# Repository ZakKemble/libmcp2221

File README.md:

# MCP2221 HID Library

This is a library for interfacing with the HID features of the [MCP2221 USB to UART and I2C/SMBus serial converter from Microchip](http://www.microchip.com/wwwproducts/Devices.aspx?product=MCP2221). The converter includes 4 GPIO pins, 3x 10-bit ADCs, 1x 5-bit DAC and more.

Microchip does provide a library for interfacing with the chip, however it is supplied as proprietary DLLs. This project aims to be an open-source and multi-platform alternative.

This library also makes use of [HIDAPI](http://www.signal11.us/oss/hidapi/).

| Feature | Status
| ------- | ------
| ADC     | Supported
| DAC     | Supported
| GPIO    | Supported
| Interrupt input        | Supported
| Clock reference output | Supported
| USB Descriptors (Manufacturer, product, serial, VID, PID) | Supported
| I2C/SMB | Limited support, WIP
| Flash password protection | Not yet implemented
| C++ and C# wrappers       | Not yet implemented

*Reading clock out duty cycle is not documented in the datasheet, but the Microchip library seems to support it.

## Documentation
[Doxygen pages](http://zkemble.github.io/libmcp2221/)

Hint:

| Function prefix | Description
| --------------- | -----------
| mcp2221_set*    | Set SRAM config, this takes immediate effect
| mcp2221_get*    | Get SRAM config
| mcp2221_save*   | Writes to flash, this setting is used at startup
| mcp2221_load*   | Read from flash
| mcp2221_read*   | Read ADC/GPIO/interrupt values

## Setting up
### Using pre-built binaries
- Copy `libmcp2221.h` to your compilers include directory (`/usr/include/` on Linux)
- Windows: Copy `./lib/win/libmcp2221.dll` to your compilers lib directory. Each program that uses libmcp2221 will need a copy of `libmcp2221.dll` in the same directory.
- Linux: Copy `./lib/unix/libmcp2221.so` and `./lib/unix/libmcp2221.a` to `/usr/lib/` (these were compiled on Debian 8.1 x64 using the HIDRAW version of HIDAPI)

### Compiling
- Download hid.c for your OS from https://github.com/signal11/hidapi ([Windows](https://raw.githubusercontent.com/signal11/hidapi/master/windows/hid.c) | [Linux (HIDRAW)](https://raw.githubusercontent.com/signal11/hidapi/master/linux/hid.c) | [Linux (LibUSB - this doesn't seem to work at the moment)](https://raw.githubusercontent.com/signal11/hidapi/master/libusb/hid.c) | [Mac](https://raw.githubusercontent.com/signal11/hidapi/master/mac/hid.c)) and [hidapi.h](https://raw.githubusercontent.com/signal11/hidapi/master/hidapi/hidapi.h)
- Place `hid.c` and `hidapi.h` files into the libmcp2221 directory
- Linux HIDAPI requires dev packages for libudev and libusb `apt-get install libudev-dev libusb-1.0-0-dev`
- Run `make`
- Copy `libmcp2221.h` to your compilers include directory (`/usr/include/` on Linux)
- Windows: Copy `libmcp2221.dll` from the bin folder to your compilers lib directory. Each program that uses libmcp2221 will need a copy of `libmcp2221.dll` in the same directory.
- Linux: Copy `libmcp2221.so` and `libmcp2221.a` from the bin folder to `/usr/lib/`

--------

Third party contents are copyrighted by their respective authors.

My productions are published under GNU GPL v3 (see License.txt).

--------

[MCP2221 HID Library](http://blog.zakkemble.co.uk/mcp2221-hid-library/)

--------

Zak Kemble

contact@zakkemble.co.uk

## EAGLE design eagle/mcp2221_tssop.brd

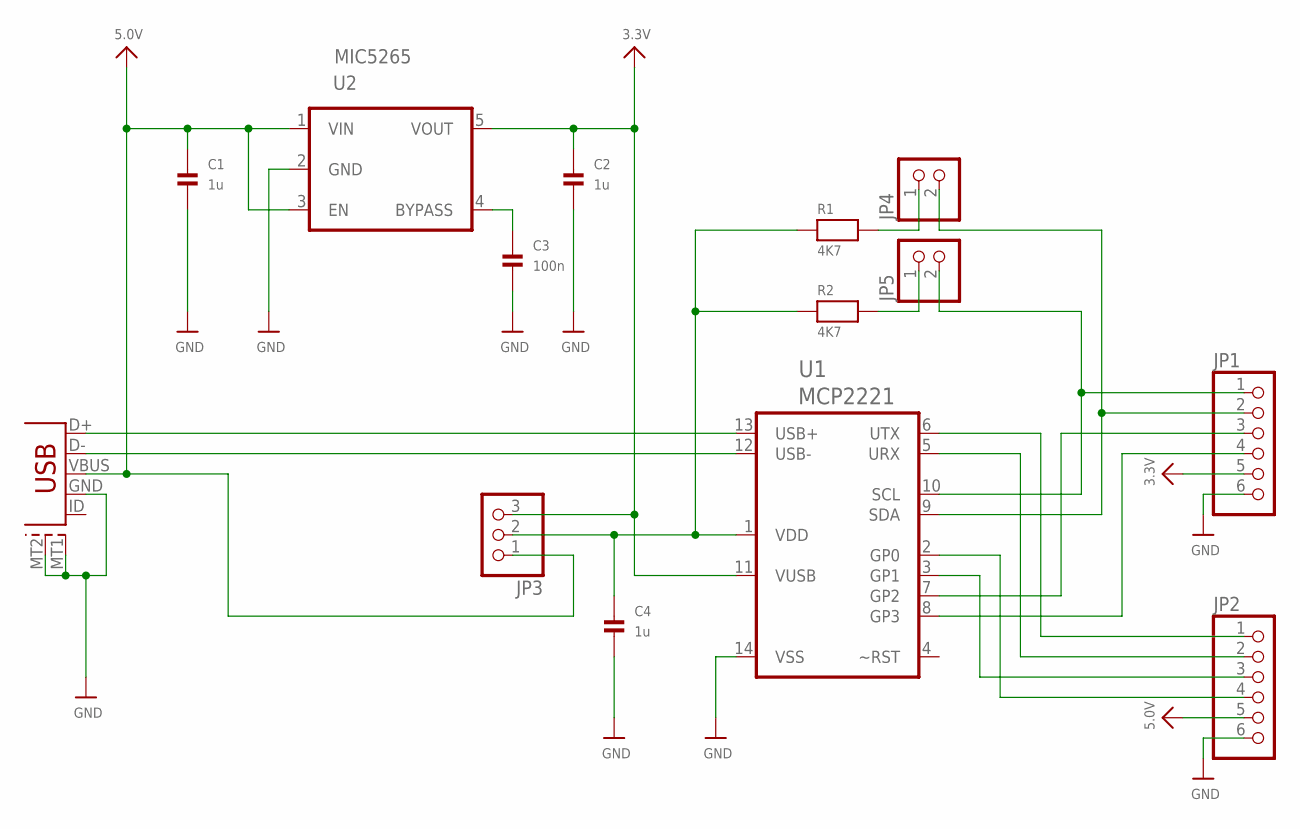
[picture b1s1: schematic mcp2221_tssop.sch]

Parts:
C1, C2, C4: 1u; 0805
C3: 100n; 0805
JP1, JP2: PINHD-1X6; 1X06
JP3: PINHD-1X3; 1X03
JP4, JP5: PINHD-1X2; 1X02
R1, R2: 4K7; 0805
U1: MCP2221; TSSOP14
U2: MIC5265; SOT95P275X110-5N
USB1: USB-MICROBLARGEPAD; USB-MICROB_LARGEPAD

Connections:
3.3V: C2.1, JP1.5, JP3.3, U1.11 (VUSB), U2.5 (VOUT)
5.0V: C1.1, JP2.5, JP3.1, U2.1 (VIN), U2.3 (EN), USB1.VBUS
GND: C1.2, C2.2, C3.2, C4.2, JP1.6, JP2.6, U1.14 (VSS), U2.2 (GND), USB1.GND, USB1.MT1 (SHEILD1), USB1.MT2 (SHEILD2)
unnamed: JP1.4, U1.8 (GP3)
unnamed: C3.1, U2.4 (BYPASS)
unnamed: U1.13 (USB+), USB1.D+
unnamed: JP1.3, U1.7 (GP2)
unnamed: C4.1, JP3.2, R1.1, R2.1, U1.1 (VDD)
unnamed: JP2.1, U1.6 (UTX)
unnamed: U1.12 (USB-), USB1.D-
unnamed: JP5.1, R2.2
unnamed: JP2.2, U1.5 (URX)
unnamed: JP2.3, U1.3 (GP1)
unnamed: JP2.4, U1.2 (GP0)
unnamed: JP4.1, R1.2
unnamed: JP1.2, JP4.2, U1.9 (SDA)
unnamed: JP1.1, JP5.2, U1.10 (SCL)

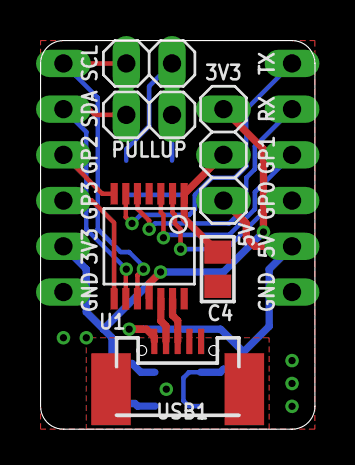
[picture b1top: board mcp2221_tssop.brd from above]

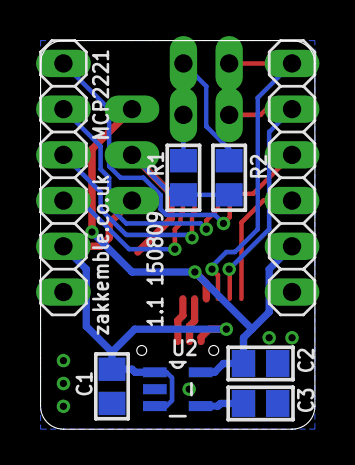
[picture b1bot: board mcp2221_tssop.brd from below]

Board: 2 copper layers, 15.2 x 21.6 mm, 14 parts (8 on the bottom side), 17 nets.

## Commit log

2015-08-13 :neckbeard: Added .gitattributes & .gitignore files
2015-08-13 First pages commit
2015-08-13 Readme fix
    Hopefully fixes a table
2015-08-14 Serial is null when not enumerated, not an empty string!
2016-02-24 Changed MCP2221_GPIO_MODE_ALT numbering to match the datasheet (1-3 instead of 0-2)
    Be sure to update any of your code that sets GPIO mode!
2016-02-24 Updated mcp2221_gpio_mode_t
2016-12-07 Fix Clock Duty Cycle
2016-12-07 Src Clock is actually 48MHz and Duty Cycle was inverted
2016-12-07 minor correction in param definition
2016-12-30 Little updates for 1.0.4 release
2016-12-30 Updates for 1.0.4
2019-11-07 Recompiled libmcp2221 with mingw 53_32, to prevent this compiler error in Qt 5.11.1 programs: libmcp2221.dll: file not recognized: File format not recognized collect2.exe: error: ld returned 1 exit s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
    Added dependencies for libmcp2221 from here:
    https://github.com/signal11/hidapi/blob/a6a622ffb680c55da0de787ff93b80280498330f/hidapi/hidapi.h
    https://github.com/signal11/hidapi/blob/a6a622ffb680c55da0de787ff93b80280498330f/windows/hid.c
    Corrected some documentation in libmcp2221.h

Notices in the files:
parts and their libraries:
microbuilder: This work is placed in the public domain, and may be freely used for commercial and non-commercial work with the following conditions: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
